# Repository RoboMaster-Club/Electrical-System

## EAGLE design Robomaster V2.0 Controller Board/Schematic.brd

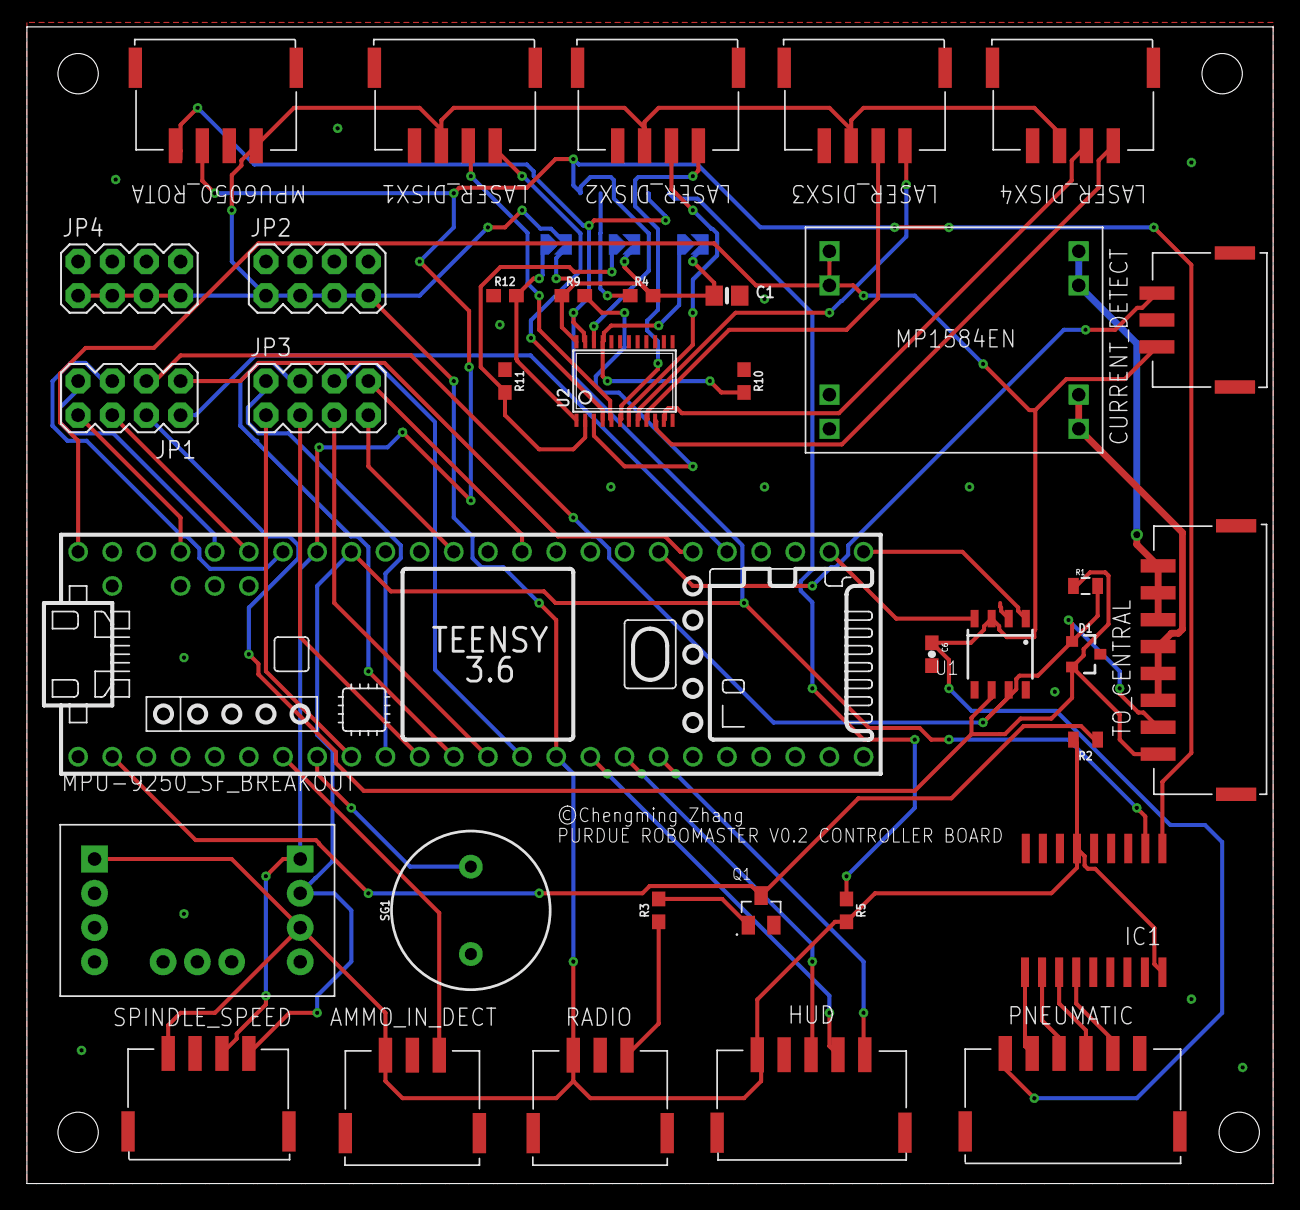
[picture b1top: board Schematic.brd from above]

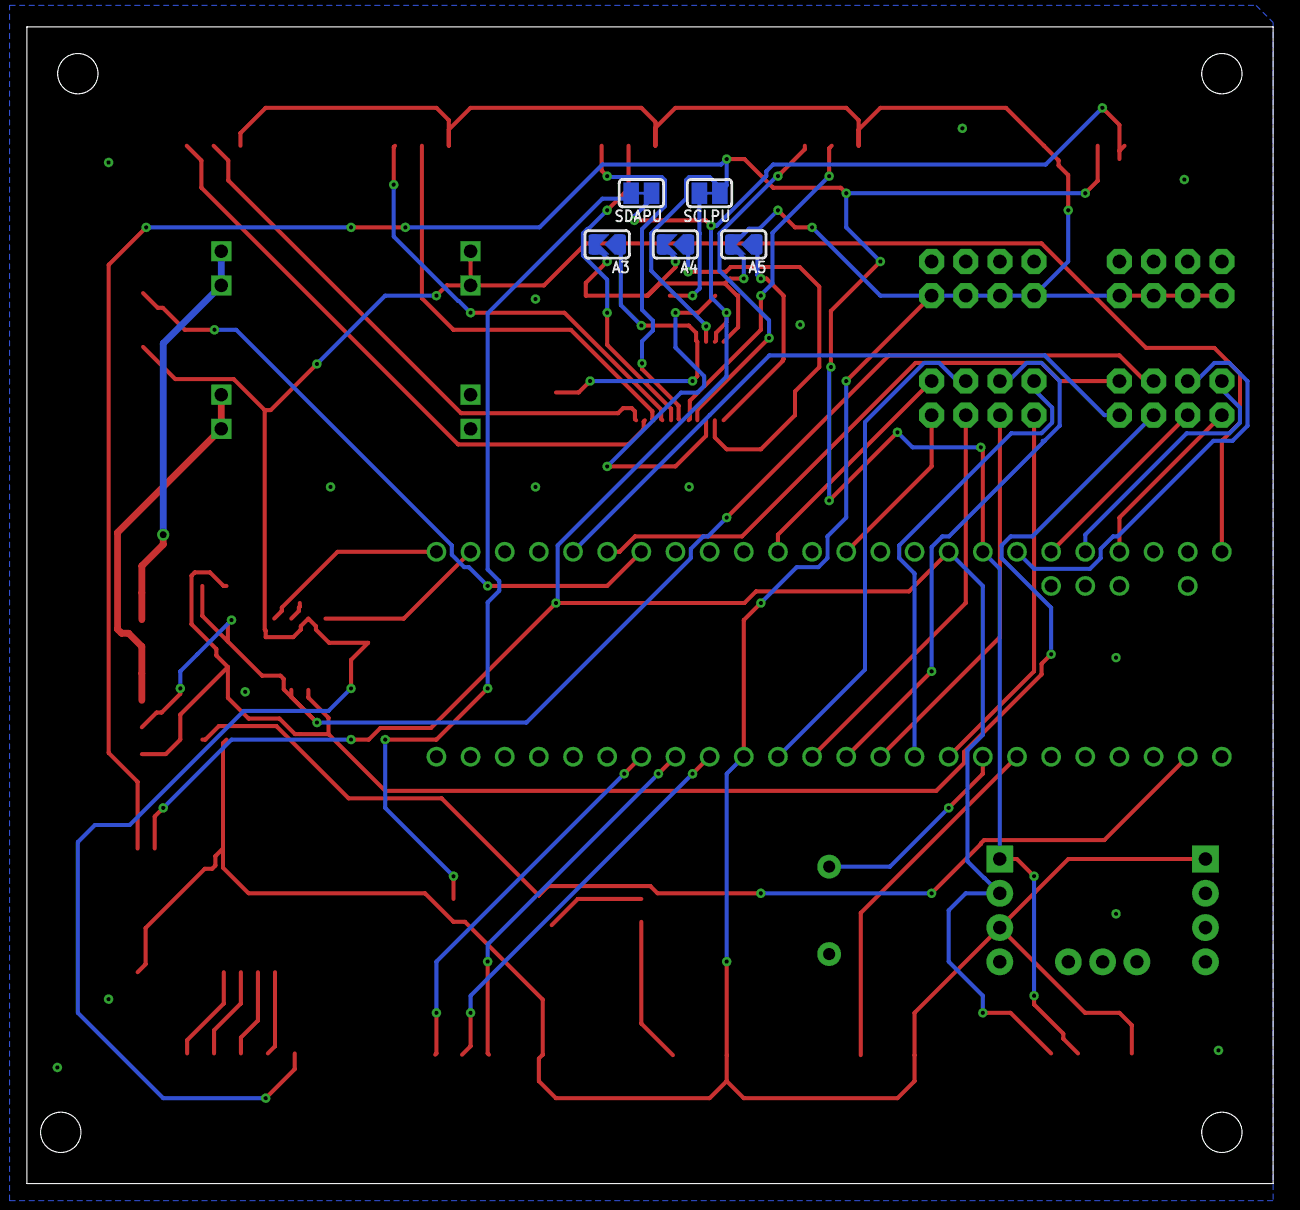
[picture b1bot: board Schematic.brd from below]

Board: 2 copper layers, 92.7 x 86.0 mm, 41 parts (5 on the bottom side), 52 nets.

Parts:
A3, A4, A5: SOLDERJUMPER_ARROW_NOPASTE
AMMO_IN_DECT: S3B-PH-SM4_TB
C1: 10uF; 0805-NO
C6: 0.1uF; 0603-CAP
CURRENT_DETECT: S3B-PH-SM4_TB
D1: PESD1CAN; SOT23-3
HUD: S5B-PH-SM4_TB
IC1: MCP23008/SO; SO18W
JP1, JP2, JP3, JP4: 2X4
LASER_DISX1, LASER_DISX2, LASER_DISX3, LASER_DISX4: S4B-PH-SM4_TB
MPU6050_ROTA: S4B-PH-SM4_TB
PNEUMATIC: S6B-PH-SM4_TB
Q1: S9013; SOT95P240X120-3N
R1: 120; 0805@1
R2: 0.3; 0805
R3, R4, R5, R9, R10, R11, R12: 10k; 0603
RADIO: S3B-PH-SM4_TB
SCLPU: SOLDERJUMPER_CLOSEDWIRE
SDAPU: SOLDERJUMPER_CLOSEDWIRE
SG1: BUZZER-PTH; BUZZER-12MM
SPINDLE_SPEED: S4B-PH-SM4_TB
TO_CENTRAL: S8B-PH-SM4_TB
U1: TJA1050; SOT96-1
U2: TCA9548APWR; TSSOP24
U$1: TEENSY_3.5/3.6_BASIC
U$2: MP1584; MP1584_AMAZON
U$4: SPARKFUN_BREAKOUT_MPU-9250

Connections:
0SCL: LASER_DISX1.2, U2.5
0SDA: LASER_DISX1.1, U2.4
1SCL: LASER_DISX2.2, U2.7
1SDA: LASER_DISX2.1, U2.6
2SCL: LASER_DISX3.2, U2.9
2SDA: LASER_DISX3.1, U2.8
3SCL: LASER_DISX4.2, U2.11
3SDA: LASER_DISX4.1, U2.10
A0: A5.1, R12.2, U2.1
A1: A4.1, R11.2, U2.2
A2: A3.1, R10.2, U2.21
A6: JP1.5, U$1.20/A6
A7: JP1.6, U$1.21/A7
A8: JP1.7, U$1.22/A8
A9: JP1.8, U$1.23/A9
AMMO_INCOM: AMMO_IN_DECT.3, U$1.5
BUZZER: SG1.+, U$1.6
CAN1RX: U1.4, U$1.34/A15
CAN1TX: U1.1, U$1.33/A14
CANH: D1.1, JP1.3, R1.2, TO_CENTRAL.2, U1.7
CANL: D1.2, JP1.4, R1.1, TO_CENTRAL.1, U1.6
CS0: JP3.7, U$1.15/A1
CURRENT_SENSE: CURRENT_DETECT.3, U$1.39/A20
GND: AMMO_IN_DECT.2, C1.2, C6.2, CURRENT_DETECT.2, D1.3, HUD.2, IC1.3, IC1.4, IC1.5, IC1.9, JP2.2, JP2.4, JP2.6, JP2.8, JP4.2, JP4.4, JP4.6, JP4.8, LASER_DISX1.4, LASER_DISX2.4, LASER_DISX3.4, LASER_DISX4.4, MPU6050_ROTA.2, PNEUMATIC.6, Q1.2, R10.1, R11.1, R12.1, RADIO.2, SG1.-, SPINDLE_SPEED.2, U1.2, U1.8, U2.12, U$1.AGND, U$1.GND, U$2.5, U$2.6, U$4.GND, U$4.SD0/AD0
MISO0: JP3.6, U$1.12/MISO
MOSI0: JP3.5, U$1.11/MOSI
unnamed: Q1.1, R3.2
unnamed: R4.1, SCLPU.2
unnamed: R5.1, SDAPU.2
unnamed: R9.2, U2.3
PNEU_1: IC1.10, PNEUMATIC.2
PNEU_2: IC1.11, PNEUMATIC.3
PNEU_3: IC1.12, PNEUMATIC.4
PNEU_4: IC1.13, PNEUMATIC.5
R1IN: R3.1, RADIO.3
R1OUT: Q1.3, R2.1, U$1.0/RX
RX2: JP3.3, U$1.9/CS
RX3: JP3.1, U$1.7
SCK0: JP3.8, U$1.13/SCK
SCL: IC1.1, MPU6050_ROTA.3, SCLPU.1, SPINDLE_SPEED.3, U2.22, U$1.19/A5/SCL, U$4.SCL
SCL1: JP1.2, U$1.37/A18
SDA: IC1.2, MPU6050_ROTA.4, SDAPU.1, SPINDLE_SPEED.4, U2.23, U$1.18/A4/SDA, U$4.SDA
SDA1: JP1.1, U$1.38/A19
SSD_CLK: HUD.4, U$1.24
SSD_DIN: HUD.5, U$1.26
SSD_LOAD: HUD.3, U$1.25
TX2: JP3.4, U$1.10/CS
TX3: JP3.2, U$1.8
VCC: A3.2, A4.2, A5.2, AMMO_IN_DECT.1, C1.1, HUD.1, IC1.6, IC1.18, JP2.1, JP2.3, JP2.5, JP2.7, JP4.1, JP4.3, JP4.5, JP4.7, LASER_DISX1.3, LASER_DISX2.3, LASER_DISX3.3, LASER_DISX4.3, MPU6050_ROTA.1, R2.2, R4.2, R5.2, R9.1, RADIO.1, SPINDLE_SPEED.1, U2.24, U$1.3V3, U$4.VDD, U$4.VDDIO
VCC_5: C6.1, CURRENT_DETECT.1, PNEUMATIC.1, U1.3, U$1.VIN, U$2.7, U$2.8
VIN_24+: TO_CENTRAL.3, TO_CENTRAL.4, TO_CENTRAL.5, U$2.1, U$2.2
VIN_24-: TO_CENTRAL.6, TO_CENTRAL.7, TO_CENTRAL.8, U$2.3, U$2.4

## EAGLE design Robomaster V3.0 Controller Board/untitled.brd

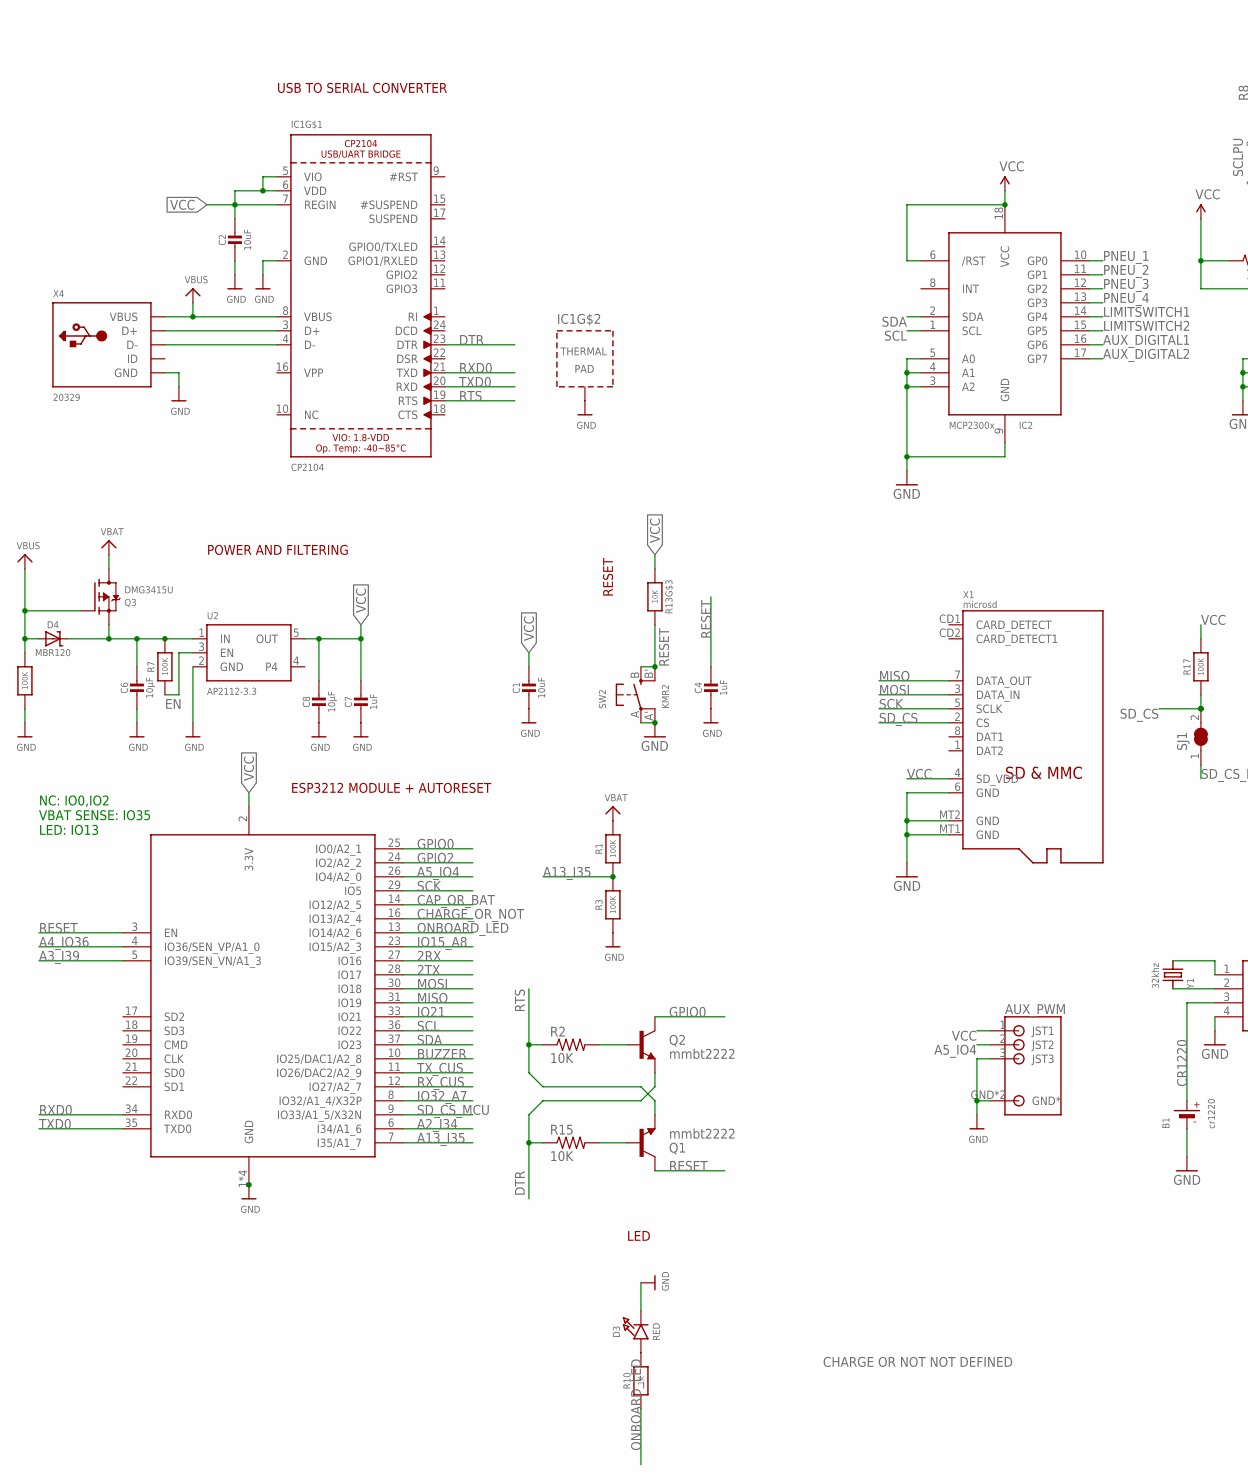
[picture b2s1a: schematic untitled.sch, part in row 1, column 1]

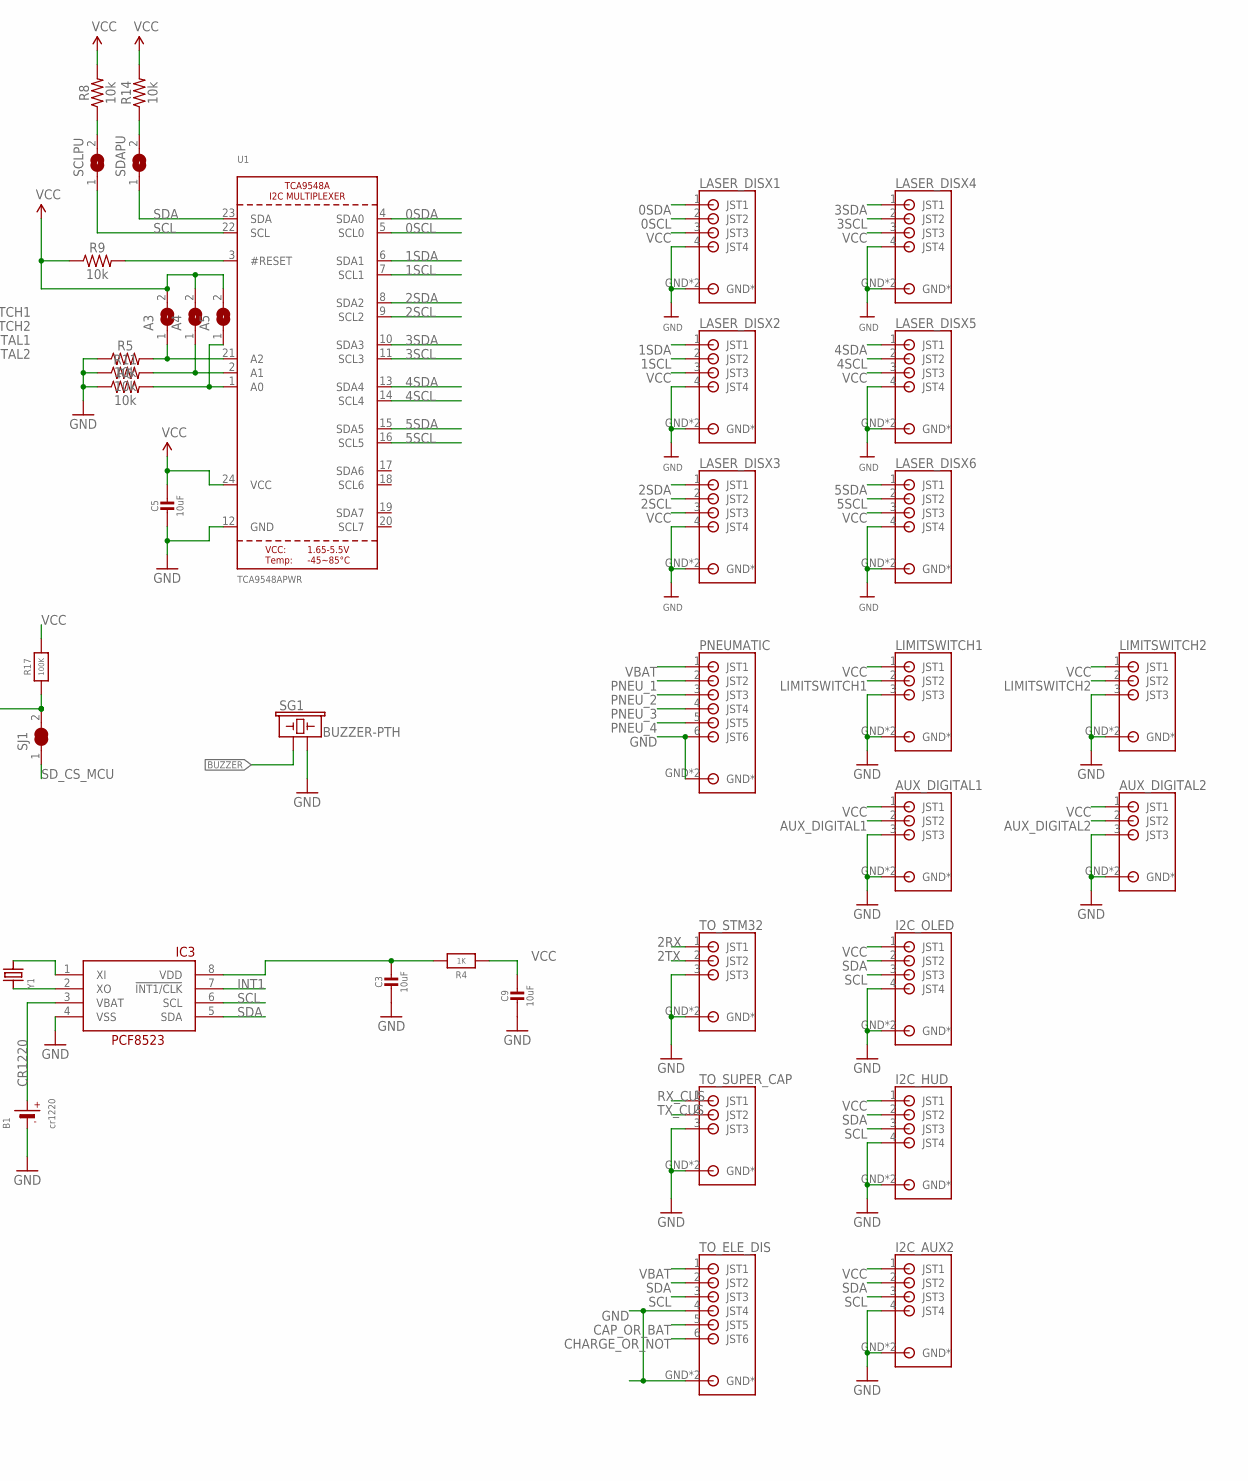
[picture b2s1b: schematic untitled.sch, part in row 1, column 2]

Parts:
A3, A4, A5: SOLDERJUMPER; SOLDERJUMPER_ARROW_NOPASTE
AUX_DIGITAL1, AUX_DIGITAL2: S3B-PH-SM4_TB
AUX_PWM: S3B-PH-SM4_TB
B1: cr1220; CR1220-2
C1, C2, C3, C5, C9: 10uF; 0805-NO
C4, C7: 1uF; 0603-NO
C6, C8: 10µF; 0805-NO
D3: RED; CHIPLED_0805_NOOUTLINE
D4: MBR120; SOD-123
I2C_AUX2, I2C_HUD, I2C_OLED: S4B-PH-SM4_TB
IC1: CP2104; QFN24_4MM_SMSC
IC2: MCP23008/SO; SO18W
IC3: PCF8523T; SOIC8_150MIL
LASER_DISX1, LASER_DISX2, LASER_DISX3, LASER_DISX4, LASER_DISX5, LASER_DISX6: S4B-PH-SM4_TB
LIMITSWITCH1, LIMITSWITCH2: S3B-PH-SM4_TB
PNEUMATIC: S6B-PH-SM4_TB
Q1, Q2: mmbt2222; SOT23-3
Q3: DMG3415U; SOT23-R
R1, R3, R7, R12, R17: 100K; 0603-NO
R2, R15: 10K; 0603-RES
R4, R10: 1K; 0603-NO
R5, R6, R8, R9, R11, R14: 10k; 0603
R13: 10K; RESPACK_4X0603
SCLPU: SOLDERJUMPERCLOSED; SOLDERJUMPER_CLOSEDWIRE
SDAPU: SOLDERJUMPERCLOSED; SOLDERJUMPER_CLOSEDWIRE
SG1: BUZZER-PTH; BUZZER-12MM
SJ1: SOLDERJUMPER_CLOSED; SOLDERJUMPER_CLOSEDWIRE
SW2: KMR2; BTN_KMR2_4.6X2.8
TO_ELE_DIS: S6B-PH-SM4_TB
TO_STM32: S3B-PH-SM4_TB
TO_SUPER_CAP: S3B-PH-SM4_TB
U1: TCA9548APWR; TSSOP24
U2: AP2112-3.3; SOT23-5
X1: microsd; MICROSD
X2: ESP32_WROOM32_SKINNY; WROOM32_SKINNY
X4: 20329; 4UCONN_20329_V2
Y1: 32khz; CRYSTAL_8X3.8

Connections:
0SCL: LASER_DISX1.2 (JST2), U1.5 (SCL0)
0SDA: LASER_DISX1.1 (JST1), U1.4 (SDA0)
1SCL: LASER_DISX2.2 (JST2), U1.7 (SCL1)
1SDA: LASER_DISX2.1 (JST1), U1.6 (SDA1)
2RX: TO_STM32.1 (JST1), X2.27 (IO16); also elsewhere on the board
2SCL: LASER_DISX3.2 (JST2), U1.9 (SCL2)
2SDA: LASER_DISX3.1 (JST1), U1.8 (SDA2)
2TX: TO_STM32.2 (JST2), X2.28 (IO17); also elsewhere on the board
3SCL: LASER_DISX4.2 (JST2), U1.11 (SCL3)
3SDA: LASER_DISX4.1 (JST1), U1.10 (SDA3)
4SCL: LASER_DISX5.2 (JST2), U1.14 (SCL4)
4SDA: LASER_DISX5.1 (JST1), U1.13 (SDA4)
5SCL: LASER_DISX6.2 (JST2), U1.16 (SCL5)
5SDA: LASER_DISX6.1 (JST1), U1.15 (SDA5)
A0: A5.1, R6.2, U1.1 (A0)
A0_DAC2: TO_SUPER_CAP.2 (JST2), X2.11 (IO26/DAC2/A2_9)
A1: A4.1, R11.2, U1.2 (A1)
A2: A3.1, R5.2, U1.21 (A2)
A2_I34: X2.6 (I34/A1_6)
A3_I39: X2.5 (IO39/SEN_VN/A1_3)
A4_IO36: X2.4 (IO36/SEN_VP/A1_0)
A5_IO4: AUX_PWM.2 (JST2), X2.26 (IO4/A2_0)
A13_I35: R1.1, R3.2, X2.7 (I35/A1_7)
AUX_DIGITAL1: AUX_DIGITAL1.2 (JST2), IC2.16 (GP6)
AUX_DIGITAL2: AUX_DIGITAL2.2 (JST2), IC2.17 (GP7)
BUZZER: SG1.+ (1), X2.10 (IO25/DAC1/A2_8)
CAP_OR_BAT: TO_ELE_DIS.5 (JST5), X2.14 (IO12/A2_5)
CHARGE_OR_NOT: TO_ELE_DIS.6 (JST6), X2.16 (IO13/A2_4)
CR1220: B1.+, IC3.3 (VBAT)
DTR: IC1.23 (DTR), Q2.2 (E), R15.1
EN: R7.1, U2.3 (EN)
GND: AUX_DIGITAL1.3 (JST3), AUX_DIGITAL1.GND (GND*), AUX_DIGITAL1.GND2 (GND*), AUX_DIGITAL2.3 (JST3), AUX_DIGITAL2.GND (GND*), AUX_DIGITAL2.GND2 (GND*), AUX_PWM.3 (JST3), AUX_PWM.GND (GND*), AUX_PWM.GND2 (GND*), B1.-, C1.2, C2.2, C3.2, C4.2, C5.2, C6.2, C7.2, C8.2, C9.2, D3.C, I2C_AUX2.4 (JST4), I2C_AUX2.GND (GND*), I2C_AUX2.GND2 (GND*), I2C_HUD.4 (JST4), I2C_HUD.GND (GND*), I2C_OLED.4 (JST4), I2C_OLED.GND (GND*), IC1.2 (GND), IC1.THERM (TP), IC2.3 (A2), IC2.4 (A1), IC2.5 (A0), IC2.9 (GND), IC3.4 (VSS), LASER_DISX1.4 (JST4), LASER_DISX1.GND (GND*), LASER_DISX1.GND2 (GND*), LASER_DISX2.4 (JST4), LASER_DISX2.GND (GND*), LASER_DISX2.GND2 (GND*), LASER_DISX3.4 (JST4), LASER_DISX3.GND (GND*), LASER_DISX3.GND2 (GND*), LASER_DISX4.4 (JST4), LASER_DISX4.GND (GND*), LASER_DISX4.GND2 (GND*), LASER_DISX5.4 (JST4), LASER_DISX5.GND (GND*), LASER_DISX5.GND2 (GND*), LASER_DISX6.4 (JST4), LASER_DISX6.GND (GND*), LASER_DISX6.GND2 (GND*), LIMITSWITCH1.3 (JST3), LIMITSWITCH1.GND (GND*), LIMITSWITCH1.GND2 (GND*), LIMITSWITCH2.3 (JST3), LIMITSWITCH2.GND (GND*), LIMITSWITCH2.GND2 (GND*), PNEUMATIC.6 (JST6), PNEUMATIC.GND (GND*), PNEUMATIC.GND2 (GND*), R3.1, R5.1, R6.1, R11.1, R12.1, SG1.- (2), SW2.A, SW2.A' (P1), TO_ELE_DIS.4 (JST4), TO_ELE_DIS.GND (GND*), TO_ELE_DIS.GND2 (GND*), TO_STM32.3 (JST3), TO_STM32.GND (GND*), TO_STM32.GND2 (GND*), TO_SUPER_CAP.3 (JST3), TO_SUPER_CAP.GND (GND*), U1.12 (GND), U2.2 (GND), X1.6 (GND), X1.MT1 (GND), X1.MT2 (GND), X2.1 (GND), X2.15 (GND), X2.38 (GND), X2.P$1 (GND), X4.BASE@1 (GND), X4.BASE@2 (GND), X4.GND, X4.SPRT@1 (GND), X4.SPRT@2 (GND), X4.SPRT@3 (GND), X4.SPRT@4 (GND); also elsewhere on the board
GPIO0: Q2.3 (C), X2.25 (IO0/A2_1)
GPIO2: X2.24 (IO2/A2_2)
INT1: IC3.7 (!INT1/CLK)
IO15_A8: X2.23 (IO15/A2_3)
IO21: X2.33 (IO21)
IO27_A10: TO_SUPER_CAP.1 (JST1), X2.12 (IO27/A2_7)
IO32_A7: X2.8 (IO32/A1_4/X32P)
LIMITSWITCH1: IC2.14 (GP4), LIMITSWITCH1.2 (JST2)
LIMITSWITCH2: IC2.15 (GP5), LIMITSWITCH2.2 (JST2)
MISO: X1.7 (DATA_OUT), X2.31 (IO19)
MOSI: X1.3 (DATA_IN), X2.30 (IO18)
unnamed: IC3.1 (XI), Y1.P$4 (2)
unnamed: IC1.3 (D+), X4.D+
unnamed: IC3.2 (XO), Y1.P$1 (1)
unnamed: C3.1, IC3.8 (VDD), R4.2
unnamed: D3.A, R10.2
unnamed: IC1.4 (D-), X4.D-
unnamed: C6.1, D4.C, Q3.2 (S), R7.2, U2.1 (IN)
unnamed: R8.1, SCLPU.2
unnamed: R14.1, SDAPU.2
unnamed: R9.2, U1.3 (#RESET)
unnamed: Q1.1 (B), R15.2
unnamed: Q2.1 (B), R2.2
ONBOARD_LED: R10.1, X2.13 (IO14/A2_6)
PNEU_1: IC2.10 (GP0), PNEUMATIC.2 (JST2)
PNEU_2: IC2.11 (GP1), PNEUMATIC.3 (JST3)
PNEU_3: IC2.12 (GP2), PNEUMATIC.4 (JST4)
PNEU_4: IC2.13 (GP3), PNEUMATIC.5 (JST5)
RESET: C4.1, Q1.3 (C), R13.6 (2), SW2.B (S), SW2.B' (S1), X2.3 (EN)
RTS: IC1.19 (RTS), Q1.2 (E), R2.1
RXD0: IC1.21 (TXD), X2.34 (RXD0)
SCK: X1.5 (SCLK), X2.29 (IO5)
SCL: I2C_AUX2.3 (JST3), I2C_HUD.3 (JST3), I2C_OLED.3 (JST3), IC2.1 (SCL), IC3.6 (SCL), SCLPU.1, TO_ELE_DIS.3 (JST3), U1.22 (SCL), X2.36 (IO22); also elsewhere on the board
SDA: I2C_AUX2.2 (JST2), I2C_HUD.2 (JST2), I2C_OLED.2 (JST2), IC2.2 (SDA), IC3.5 (SDA), SDAPU.1, TO_ELE_DIS.2 (JST2), U1.23 (SDA), X2.37 (IO23); also elsewhere on the board
SD_CS: R17.1, SJ1.2, X1.2 (CS)
SD_CS_MCU: SJ1.1, X2.9 (IO33/A1_5/X32N)
TXD0: IC1.20 (RXD), X2.35 (TXD0)
VBAT: PNEUMATIC.1 (JST1), Q3.3 (D), R1.2, TO_ELE_DIS.1 (JST1)
VBUS: D4.A, IC1.8 (VBUS), Q3.1 (G), R12.2, X4.VBUS
VCC: A3.2, A4.2, A5.2, AUX_DIGITAL1.1 (JST1), AUX_DIGITAL2.1 (JST1), AUX_PWM.1 (JST1), C1.1, C2.1, C5.1, C7.1, C8.1, C9.1, I2C_AUX2.1 (JST1), I2C_HUD.1 (JST1), I2C_OLED.1 (JST1), IC1.5 (VIO), IC1.6 (VDD), IC1.7 (REGIN), IC2.6 (/RST), IC2.18 (VCC), LASER_DISX1.3 (JST3), LASER_DISX2.3 (JST3), LASER_DISX3.3 (JST3), LASER_DISX4.3 (JST3), LASER_DISX5.3 (JST3), LASER_DISX6.3 (JST3), LIMITSWITCH1.1 (JST1), LIMITSWITCH2.1 (JST1), R4.1, R8.2, R9.1, R13.3 (1), R14.2, R17.2, U1.24 (VCC), U2.5 (OUT), X1.4 (SD_VDD), X2.2 (3.3V); also elsewhere on the board

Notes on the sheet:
POWER AND FILTERING
RESET
USB TO SERIAL CONVERTER
LED
ESP3212 MODULE + AUTORESET
NC: IO0,IO2 VBAT SENSE: IO35 LED: IO13
CHARGE OR NOT NOT DEFINED

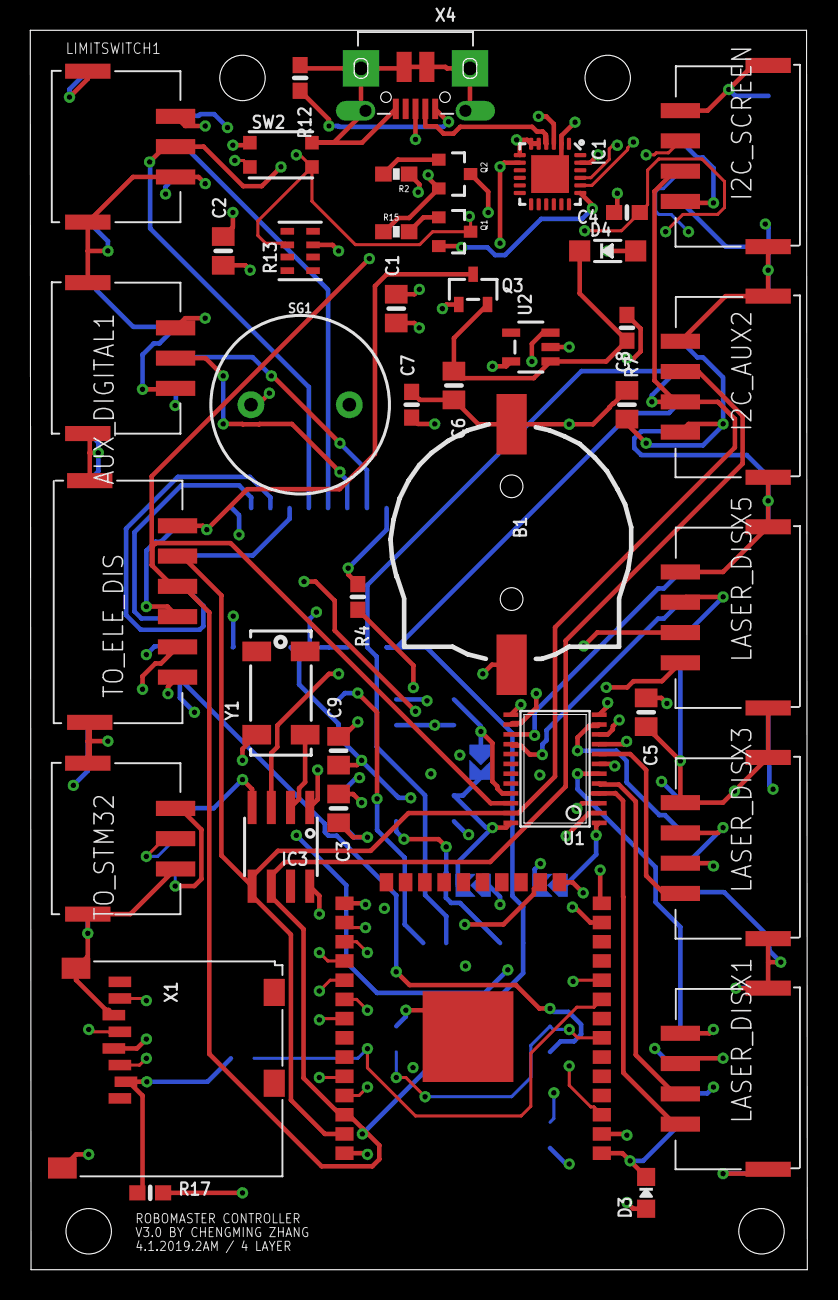
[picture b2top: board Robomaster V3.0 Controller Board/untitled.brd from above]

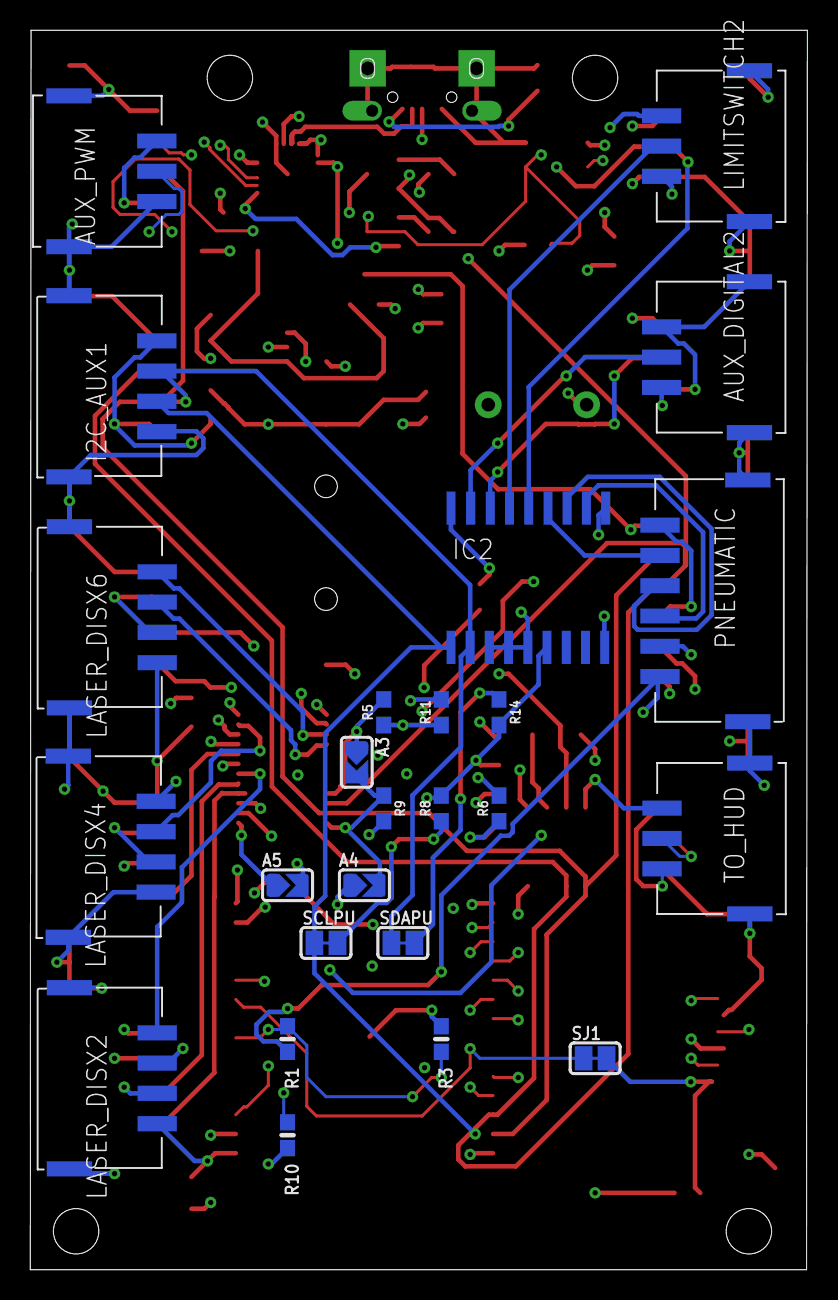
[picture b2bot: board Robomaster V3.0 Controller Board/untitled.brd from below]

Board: 4 copper layers, 51.3 x 81.9 mm, 66 parts (25 on the bottom side), 62 nets.

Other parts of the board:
I2C_AUX1, I2C_SCREEN: S4B-PH-SM4_TB
TO_HUD: S3B-PH-SM4_TB

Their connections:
2RX: TO_HUD.1; also elsewhere on the board
2TX: TO_HUD.2; also elsewhere on the board
GND: I2C_AUX1.4, I2C_AUX1.GND, I2C_AUX1.GND2, I2C_SCREEN.4, I2C_SCREEN.GND, I2C_SCREEN.GND2, TO_HUD.3, TO_HUD.GND, TO_HUD.GND2; also elsewhere on the board
SCL: I2C_AUX1.3, I2C_SCREEN.3; also elsewhere on the board
SDA: I2C_AUX1.2, I2C_SCREEN.2; also elsewhere on the board
VCC: I2C_AUX1.1, I2C_SCREEN.1; also elsewhere on the board

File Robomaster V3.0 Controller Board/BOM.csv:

Part,Value,Device,Package,Description,BOM,PROD_ID,SF_SKU,VALUE
AUX_DIGITAL1,S3B-PH-SM4_TB,S3B-PH-SM4_TB,S3B-PH-SM4_TB,,,,,
AUX_DIGITAL2,S3B-PH-SM4_TB,S3B-PH-SM4_TB,S3B-PH-SM4_TB,,,,,
AUX_PWM,S3B-PH-SM4_TB,S3B-PH-SM4_TB,S3B-PH-SM4_TB,,,,,
B1,cr1220,BATTERYCR1220_2,CR1220-2,CR1220 SMT - Digikey: 3001K-ND,,,,
C1,10uF,CAP_CERAMIC0805-NOOUTLINE,0805-NO,Ceramic Capacitors,,,,
C2,10uF,CAP_CERAMIC0805-NOOUTLINE,0805-NO,Ceramic Capacitors,,,,
C3,10uF,CAP_CERAMIC0805-NOOUTLINE,0805-NO,Ceramic Capacitors,,,,
C4,1uF,CAP_CERAMIC0603_NO,0603-NO,Ceramic Capacitors,,,,
C5,10uF,CAP_CERAMIC0805-NOOUTLINE,0805-NO,Ceramic Capacitors,,,,
C6,10µF,CAP_CERAMIC0805-NOOUTLINE,0805-NO,Ceramic Capacitors,,,,
C7,1uF,CAP_CERAMIC0603_NO,0603-NO,Ceramic Capacitors,,,,
C8,10µF,CAP_CERAMIC0805-NOOUTLINE,0805-NO,Ceramic Capacitors,,,,
C9,10uF,CAP_CERAMIC0805-NOOUTLINE,0805-NO,Ceramic Capacitors,,,,
D3,RED,LED0805_NOOUTLINE,CHIPLED_0805_NOOUTLINE,LED,,,,
D4,MBR120,DIODE-SCHOTTKYSOD-123,SOD-123,,,,,
I2C_AUX1,S4B-PH-SM4_TB,S4B-PH-SM4_TB,S4B-PH-SM4_TB,,,,,
I2C_AUX2,S4B-PH-SM4_TB,S4B-PH-SM4_TB,S4B-PH-SM4_TB,,,,,
I2C_SCREEN,S4B-PH-SM4_TB,S4B-PH-SM4_TB,S4B-PH-SM4_TB,,,,,
IC1,CP2104,CP2104,QFN24_4MM_SMSC,CP2104 - USB to UART Bridge,,,,
IC2,MCP23008/SO,MCP23008/SO,SO18W,MCP23008,,,,
IC3,PCF8523T,RTC_PCF8523T,SOIC8_150MIL,,,,,
LASER_DISX1,S4B-PH-SM4_TB,S4B-PH-SM4_TB,S4B-PH-SM4_TB,,,,,
LASER_DISX2,S4B-PH-SM4_TB,S4B-PH-SM4_TB,S4B-PH-SM4_TB,,,,,
LASER_DISX3,S4B-PH-SM4_TB,S4B-PH-SM4_TB,S4B-PH-SM4_TB,,,,,
LASER_DISX4,S4B-PH-SM4_TB,S4B-PH-SM4_TB,S4B-PH-SM4_TB,,,,,
LASER_DISX5,S4B-PH-SM4_TB,S4B-PH-SM4_TB,S4B-PH-SM4_TB,,,,,
LASER_DISX6,S4B-PH-SM4_TB,S4B-PH-SM4_TB,S4B-PH-SM4_TB,,,,,
LIMITSWITCH1,S3B-PH-SM4_TB,S3B-PH-SM4_TB,S3B-PH-SM4_TB,,,,,
LIMITSWITCH2,S3B-PH-SM4_TB,S3B-PH-SM4_TB,S3B-PH-SM4_TB,,,,,
PNEUMATIC,S6B-PH-SM4_TB,S6B-PH-SM4_TB,S6B-PH-SM4_TB,,,,,
Q1,mmbt2222,TRANSISTOR_NPNSOT23-3,SOT23-3,Transistor NPN,,,,
Q2,mmbt2222,TRANSISTOR_NPNSOT23-3,SOT23-3,Transistor NPN,,,,
Q3,DMG3415U,MOSFET-P,SOT23-R,P-Channel Mosfet,,,,
R1,100K,RESISTOR_0603_NOOUT,0603-NO,Resistors,,,,
R2,10K,10KOHM-1/10W-1%(0603)0603,0603-RES,RES-00824,,RES-00824,,10K
R3,100K,RESISTOR_0603_NOOUT,0603-NO,Resistors,,,,
R4,1K,RESISTOR_0603_NOOUT,0603-NO,Resistors,,,,
R5,10k,10KOHM-0603-1/10W-1%,603,10kΩ resistor,,RES-00824,,10k
R6,10k,10KOHM-0603-1/10W-1%,603,10kΩ resistor,,RES-00824,,10k
R7,100K,RESISTOR_0603_NOOUT,0603-NO,Resistors,,,,
R8,10k,10KOHM-0603-1/10W-1%,603,10kΩ resistor,,RES-00824,,10k
R9,10k,10KOHM-0603-1/10W-1%,603,10kΩ resistor,,RES-00824,,10k
R10,1K,RESISTOR_0603_NOOUT,0603-NO,Resistors,,,,
R11,10k,10KOHM-0603-1/10W-1%,603,10kΩ resistor,,RES-00824,,10k
R12,100K,RESISTOR_0603_NOOUT,0603-NO,Resistors,,,,
R13,10K,RESISTOR_4PACK,RESPACK_4X0603,Resistor Packs (4 resistors),,,,
R14,10k,10KOHM-0603-1/10W-1%,603,10kΩ resistor,,RES-00824,,10k
R15,10K,10KOHM-1/10W-1%(0603)0603,0603-RES,RES-00824,,RES-00824,,10K
R17,100K,RESISTOR_0603_NOOUT,0603-NO,Resistors,,,,
SG1,BUZZER-PTH,BUZZER-PTH,BUZZER-12MM,Buzzer,,COMP-08253,COM-07950,
SW2,KMR2,SWITCH_TACT_SMT4.6X2.8,BTN_KMR2_4.6X2.8,SMT Tact Switches,,,,
TO_ELE_DIS,S6B-PH-SM4_TB,S6B-PH-SM4_TB,S6B-PH-SM4_TB,,,,,
TO_HUD,S3B-PH-SM4_TB,S3B-PH-SM4_TB,S3B-PH-SM4_TB,,,,,
TO_STM32,S3B-PH-SM4_TB,S3B-PH-SM4_TB,S3B-PH-SM4_TB,,,,,
U1, TCA9548APWR,TCA9548A,TSSOP24,TCA9548A I2C Multiplexer,,,,
U2,AP2112-3.3,VREG_SOT23-5,SOT23-5,SOT23-5 Fixed Voltage Regulators,,,,
X1,microsd,MICROSD,MICROSD,MicroSD/Transflash Card Holder with SPI pinout,,,,
X2,ESP32_WROOM32_SKINNY,ESP32_WROOM32_SKINNY,WROOM32_SKINNY,,,,,
X4,20329,USB_MICRO_20329_V2,4UCONN_20329_V2,USB Connectors,,,,
Y1,32khz,CRYSTAL8.0X3.8,CRYSTAL_8X3.8,Crystals,,,,

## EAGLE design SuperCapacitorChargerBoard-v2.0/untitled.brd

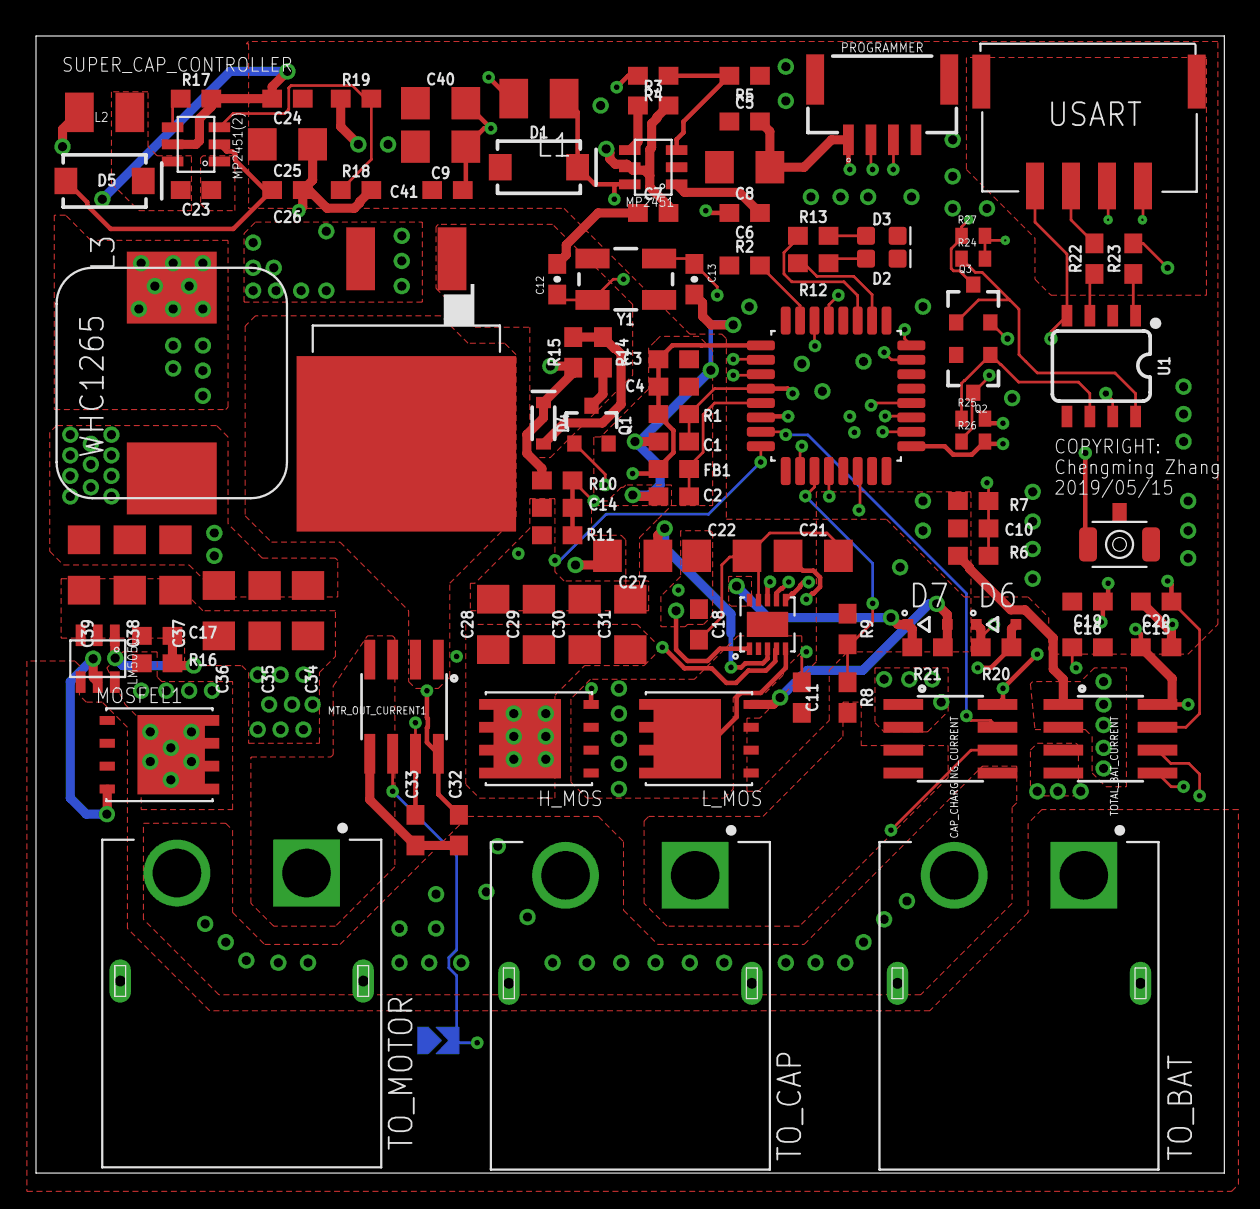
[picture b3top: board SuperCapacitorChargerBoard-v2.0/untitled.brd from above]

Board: 4 copper layers, 66.0 x 63.2 mm, 103 parts (1 on the bottom side), 61 nets.

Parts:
BW_SEL_HIGHT_RES: SOLDERJUMPER_ARROW_NOPASTE
C1, C3, C4, C5, C6, C7, C10, C11, C14, C15, C17, C18, C19, C23, C24, C26, C32, C41: 0.1uF; 0603
C2: 4.7uF; 0603
C8, C9, C21, C22, C25, C27, C28, C29, C30, C31, C40: 4.7uF; 1206
C12, C13: 22p; 0603-CAP
C16, C20, C33: 1nF; 0603
C34, C35, C36, C37, C38, C39: 22uF; 1206
CAP_CHARGING_CURRENT: ACS723; SO08
D1, D5: 3A/40V/500mV; SMA-DIODE
D2: RED; LED-0603
D3: GREEN; LED-0603
D4: MMSZ5242/12v; SOD-323
D6, D7: 1N4148WS; SOD323
FB1: 600Ω/1.8A; 0603
H_MOS: BSC018N04; TRANS_BSC076N06NS3-G
L1, L2: SWPA3012S4R7MT; L3230M
L3: WHC1265-10UH
LM5050: LM5050; TSOT-23-6-SOT-23-6
L_MOS: BSC018N04; TRANS_BSC076N06NS3-G
MOSFEL1: BSC018N04; TRANS_BSC076N06NS3-G
MOTOR_MOS: IRF4905S; D2PAK
MP2451, MP2451(2): MP2451; TSOT-23-6-SOT-23-6
MTR_OUT_CURRENT1: ACS723; SO08
PROGRAMMER: BM04B-GHS-TBT
Q1: S8050/25v 500mW; SOT23-3
Q2, Q3: NPN; SOT23-3
R1, R2: 10K; 0603
R3, R17: 100K; 0603
R4, R18: 124K; 0603
R5: 40.2k; 0603
R6, R8, R10: 16.2k; 0603
R7, R9, R11: 1.69k; 0603
R12, R13: 1k; 0603
R14, R16: 100; 0603
R15: 10k; 0603
R19: 8.87k; 0603
R20, R21: 470; 0603
R22, R23: 220; 0603
R24, R25, R26, R27: 10K; C0402
RESET: !RST; SWITCH-TACT-B3U-1100P-B
TOTAL_BAT_CURRENT: ACS723; SO08
TO_BAT: XT60PW-M; AMASS_XT60PW-M
TO_CAP: XT60PW-M; AMASS_XT60PW-M
TO_MOTOR: XT60PW-M; AMASS_XT60PW-M
U1: DUAL-OPTOISOLATOR_SOIC8; SO08
U$1: STM32F334K8T; QFP80P900X900X160-32N
U$6: MP1907GQ-Z; QFN10
USART: S4B-PH-SM4_TB
Y1: 16MHz; CRYSTAL-SMD-5X3.2-4PAD

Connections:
3V3_FB: MP2451.PIN3, R4.1, R5.2
12V_FB: MP2451(2).PIN3, R18.1, R19.2
BAT_VSENSE: C10.1, R6.1, R7.2, U$1.10
BW_SEL: BW_SEL_HIGHT_RES.2, CAP_CHARGING_CURRENT.6, MTR_OUT_CURRENT1.6, TOTAL_BAT_CURRENT.6
CAP_CURRENT_SENSE: C16.1, CAP_CHARGING_CURRENT.7, U$1.7
CAP_VSENSE: C11.1, R8.1, R9.2, U$1.11
DRV_EN: U$1.20, U$6.6
DRV_H: D6.A, H_MOS.4, R20.2
DRV_HS_IN: U$1.18, U$6.7
DRV_L: D7.A, L_MOS.4, R21.2
DRV_LS_IN: U$1.19, U$6.8
GND: BW_SEL_HIGHT_RES.1, C1.2, C2.2, C3.2, C4.2, C5.1, C7.1, C8.2, C9.2, C10.2, C11.2, C12.2, C13.2, C14.2, C15.2, C16.2, C17.2, C19.2, C20.2, C24.1, C25.2, C26.1, C28.2, C29.2, C30.2, C31.2, C32.2, C33.2, C34.2, C35.2, C36.2, C37.2, C38.2, C39.2, C40.2, C41.1, CAP_CHARGING_CURRENT.5, D1.A, D2.C, D3.C, D5.A, LM5050.PIN2, LM5050.PIN3, L_MOS.1, L_MOS.2, L_MOS.3, MP2451.PIN2, MP2451(2).PIN2, MTR_OUT_CURRENT1.5, PROGRAMMER.1, Q1.2, Q2.2, R2.1, R5.1, R7.1, R9.1, R11.1, R19.1, RESET.2, TOTAL_BAT_CURRENT.5, TO_BAT.2, TO_CAP.2, TO_MOTOR.2, U1.2, U1.5, U$1.16, U$1.32
IN_CURRENT_SENSE: C20.1, TOTAL_BAT_CURRENT.7, U$1.6
LEDG: R13.1, U$1.27
LEDR: R12.1, U$1.26
MTR_CURRENT_SENSE: C33.1, MTR_OUT_CURRENT1.7, U$1.8
MTR_EN: Q1.1, U$1.14
unnamed: D2.A, R12.2
unnamed: MP2451.PIN4, R3.1
unnamed: D3.A, R13.2
unnamed: C6.1, MP2451.PIN1
unnamed: C2.1, FB1.1, U$1.5
unnamed: C6.2, D1.C, L1.1, MP2451.PIN6
unnamed: R2.2, U$1.31
unnamed: Q1.3, R14.2
unnamed: D4.A, MOTOR_MOS.1, R14.1, R15.2
unnamed: C17.1, LM5050.PIN1, R16.1
unnamed: C18.2, C21.2, C22.2, U$6.9
unnamed: LM5050.PIN5, MOSFEL1.4
unnamed: MP2451(2).PIN4, R17.1
unnamed: C23.1, MP2451(2).PIN1
unnamed: C23.2, D5.C, L2.1, MP2451(2).PIN6
unnamed: C27.1, U$6.3
unnamed: D6.C, R20.1, U$6.4
unnamed: R23.1, U1.1
unnamed: D7.C, R21.1, U$6.10
unnamed: R22.1, U1.3
NRST: C1.1, R1.2, RESET.1, U$1.4
OSC_IN: C12.1, U$1.2, Y1.3
OSC_OUT: C13.1, U$1.3, Y1.1
OUT1N: Q3.1, R24.1, U1.8
OUT2N: Q2.1, R25.1, U1.6
OUT_VSENSE: C14.1, R10.1, R11.2, U$1.12
RX: Q2.3, R26.1, U$1.30
SIG_GND: Q3.2, U1.4, U1.7, USART.4
SIG_RX: R22.2, USART.3
SIG_TX: Q3.3, R27.1, USART.2
SIG_VCC: R24.2, R27.2, USART.1
SYS_SWCLK: PROGRAMMER.2, U$1.24
SYS_SWDIO: PROGRAMMER.3, U$1.23
TX: R23.2, U$1.29
VBAT: C7.2, C24.2, LM5050.PIN6, MOSFEL1.5, MOSFEL1.6, MOSFEL1.7, MOSFEL1.8, MOSFEL1.9, MP2451.PIN5, MP2451(2).PIN5, R3.2, R6.2, R16.2, R17.2, TOTAL_BAT_CURRENT.1, TOTAL_BAT_CURRENT.2
VBAT_RAW: LM5050.PIN4, MOSFEL1.1, MOSFEL1.2, MOSFEL1.3, TO_BAT.1
VCAP: CAP_CHARGING_CURRENT.3, CAP_CHARGING_CURRENT.4, R8.2, TO_CAP.1
VCC: C3.1, C4.1, C5.2, C8.1, C9.1, C15.1, C19.1, C32.1, C40.1, C41.2, CAP_CHARGING_CURRENT.8, FB1.2, L1.2, MTR_OUT_CURRENT1.8, PROGRAMMER.4, R1.1, R4.2, R25.2, R26.2, TOTAL_BAT_CURRENT.8, U$1.1, U$1.17
VCC_12V: C18.1, C21.1, C22.1, C25.1, C26.2, L2.2, R18.2, U$6.1
VMTR: MTR_OUT_CURRENT1.3, MTR_OUT_CURRENT1.4, TO_MOTOR.1
VMTR_T: MOTOR_MOS.2, MTR_OUT_CURRENT1.1, MTR_OUT_CURRENT1.2
VOUT: C34.1, C35.1, C36.1, C37.1, C38.1, C39.1, CAP_CHARGING_CURRENT.1, CAP_CHARGING_CURRENT.2, D4.C, L3.P$2, MOTOR_MOS.3, R10.2, R15.1
VSW_NODE: C27.2, H_MOS.1, H_MOS.2, H_MOS.3, L3.P$1, L_MOS.5, L_MOS.6, L_MOS.7, L_MOS.8, L_MOS.9, U$6.5
VSW_T: C28.1, C29.1, C30.1, C31.1, H_MOS.5, H_MOS.6, H_MOS.7, H_MOS.8, H_MOS.9, TOTAL_BAT_CURRENT.3, TOTAL_BAT_CURRENT.4

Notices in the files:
Robomaster V2.0 Controller Board/Schematic.brd:
©Chengming Zhang
parts and their libraries:
microbuilder: This work is placed in the public domain, and may be freely used for commercial and non-commercial work with the following conditions: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
SparkFun-Capacitors: Licensing: Creative Commons ShareAlike 4.0 International - https://creativecommons.org/licenses/by-sa/4.0
